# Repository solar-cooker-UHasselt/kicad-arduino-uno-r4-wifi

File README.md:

# solar-cooker-kicad-arduino-uno-r4-wifi

## TODO

- USB connector footprint giving DRC errors
- fix other remaining DRC errors
- complete BOM data
- check supplier if stock is still available
- check if alternative parts are a valid replacement

## Schematic importing errors

- Parameter Set not currently supported.
- Blanket not currently supported.

## Board improting errors

- Altium layer (71) has no KiCad equivalent. It has been moved to KiCad layer Eco1_User.
- Altium layer (72) has no KiCad equivalent. It has been moved to KiCad layer Eco1_User.
- Footprint J3 pad 1-6 uses a complex pad stack (not yet supported.)
- Footprint J6 pad 1-6 uses a complex pad stack (not yet supported.)

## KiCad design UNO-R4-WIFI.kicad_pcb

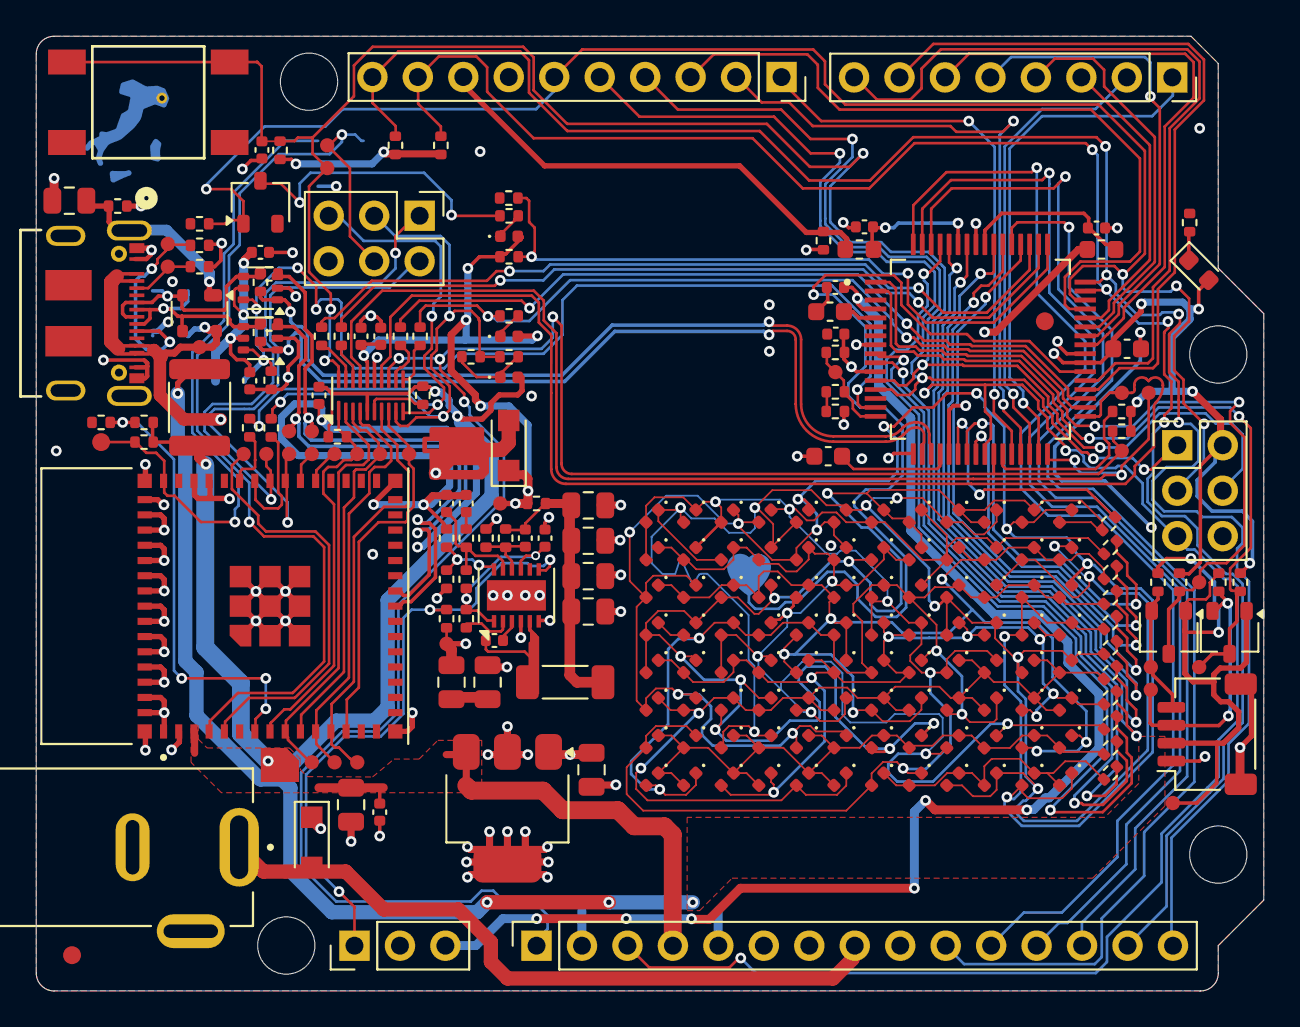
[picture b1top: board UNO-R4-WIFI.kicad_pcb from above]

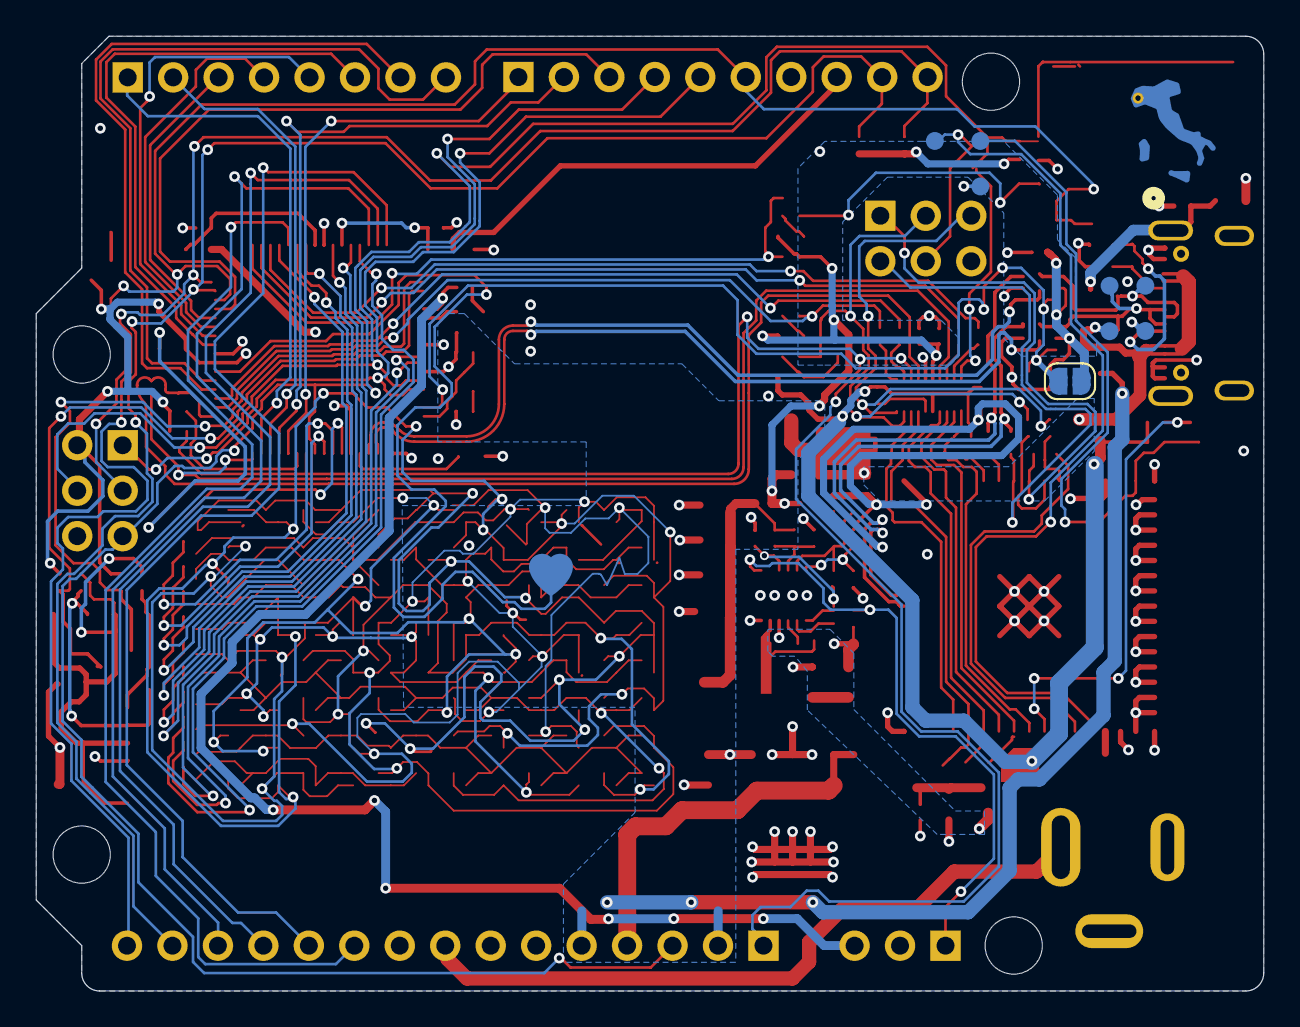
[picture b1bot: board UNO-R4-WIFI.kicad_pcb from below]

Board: 4 copper layers, 68.6 x 53.3 mm, 262 parts (9 on the bottom side), 121 nets.

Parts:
3V3_IC1, 3V3_TOP1, 5V_TOP1: TP-0.8MM
BUCK_IN_TOP1: TP-0.8MM
C1: DNP; C_0402_1005Metric
C2, C5, C9: 4.7uF; C_0603_1608Metric
C3, C7, C8, C11, C12, C25, C26, C29, C30: 100nF; C_0402_1005Metric
C6, C20, C24: 1uF; C_0402_1005Metric
C10, C13, C15, C16, C17, C18, C19, C28: 22uF; C_0805_2012Metric
C14: 33pF; C_0402_1005Metric
C21: 4.7nF; C_0805_2012Metric
C22: 1nF; C_0402_1005Metric
C23: 100pF; C_0402_1005Metric
CC1, CC2: TP-0.8MM
D1, D2, D3, D4, D5, D6, D7, D8, D9, D10, D11, D12, D13, D14, D15, D16, D17, D18, D19, D20, D21, D22, D23, D24, D25, D26, D27, D28, D29, D30, D31, D32, D33, D34, D35, D36, D37, D38, D39, D40, D41, D42, D43, D44, D45, D46, D47, D48, D49, D50, D51, D52, D53, D54, D55, D56, D57, D58, D59, D60, D61, D62, D63, D64, D65, D66, D67, D68, D69, D70, D71, D72, D73, D74, D75, D76, D77, D78, D79, D80, D81, D82, D83, D84, D85, D86, D87, D88, D89, D90, D91, D92, D93, D94, D95, D96: 150040RS73240; LED_0402_1005Metric
D97: PRTR5V0U2X,215; SOT-143
D98, D99: PMEG6020AELRX; Nexperia_CFP3_SOD-123W
D+1: TP-1.00MM
D+_TOP1: TP-0.8MM
D-1: TP-1.00MM
D-_TOP1: TP-0.8MM
DL1, DL2, DL4: APT1608YC; LED_0402_1005Metric
DL3: HSMG-C190; LED_0603_1608Metric
ESP_DOWNLOAD_BOTTOM1: TP-1.00MM
ESP_DOWNLOAD_TOP1: TP-0.8MM
ESP_EN_BOTTOM1: TP-1.00MM
ESP_EN_TOP1: TP-0.8MM; TP-1.00MM
ESP_IO1, ESP_IO4, ESP_IO5, ESP_IO6, ESP_IO7, ESP_IO8, ESP_IO9: TP-0.8MM
ESP_MTCK1: TP-0.8MM
ESP_MTDI1: TP-0.8MM
ESP_MTDO1: TP-0.8MM
ESP_MTMS1: TP-0.8MM
EXT_SCL1: TP-0.8MM
EXT_SDA1: TP-0.8MM
F1: MF-MSMF050-2; Fuse_1812_4532Metric
Fiducial_1, Fiducial_2: Fiducial mark 1mm with 2mm solder; Fiducial_1mm_Mask2mm
GND1, GND2: TP-1.00MM
H1, H2, H3, H4: MountingHole; MountingHole_3.2mm_M3_ISO7380
IC1, IC2: 74LVC1G3157DW-7; SOT-363_SC-70-6
IC3: ISL854102FRZ-T; DFN-12-1EP_3x4mm_P0.5mm_EP1.7x3.3mm
IC4: SGM2205-3.3XKC3G/TR; SOT-223
J1: GPHA-1X03; PinHeader_1x03_P2.54mm_Vertical
J2: SSQ-110-01-G-S; PinSocket_1x10_P2.54mm_Vertical
J3, J9: GPHA-2X03; PinHeader_2x03_P2.54mm_Vertical
J4: SSQ-108-01-G-S; PinSocket_1x08_P2.54mm_Vertical
J5: SSQ-115-01-G-S; PinSocket_1x15_P2.54mm_Vertical
J6: SM04B-SRSS-TB; JST_SH_SM04B-SRSS-TB_1x04-1MP_P1.00mm_Horizontal
J7: CX90B-16P
J8: EJ508A
L1, L2: BLM18PG471SN1D; L_0603_1608Metric
L3: PMF42-103MN; L_1806_4516Metric
LOVE1: TP-1.00MM
M1: ESP32-S3-MINI-1-N8
MD1: TP-0.8MM
P400_SCL1, P401_SDA1: TP-0.8MM
Q1, Q2, Q3: 2N7002KT1G; SOT-23W
R1, R3, R26, R35, R38, R43, R44, R49, R52, R56, R57, R58, R59: 100k; R_0402_1005Metric
R2, R14, R16, R20, R22, R23, R24, R25, R27, R28, R29, R30, R31, R32, R33, R34: 330; R_0402_1005Metric
R4, R5, R6, R7, R8, R9, R10, R11, R12, R13, R15, R19, R50, R51: 5.1k; R_0402_1005Metric
R17, R18, R21, R36, R37, R42, R45, R46, R47, R48, R53, R54, R55: 0; R_0402_1005Metric
R39: 1M; R_0402_1005Metric
R40, R60: 13k; R_0402_1005Metric
R41: 249k; R_0402_1005Metric
RES1: TP-0.8MM
SJ1: SMD solder JUMPER 0805; SolderJumper-2_P1.3mm_Open_RoundedPad1.0x1.5mm
SW1: FSM2JSMATR
SWCLK1: TP-0.8MM
SWDIO1: TP-0.8MM
U1: R7FA4M1AB3CFM#AA0
U2: TXB0108DQSR; USON-20_2x4mm_P0.4mm
VBUS_CONN1: TP-1.00MM
VCONN_TOP1: TP-0.8MM
VIN_TOP1: TP-0.8MM
uC_VBUS1: TP-0.8MM

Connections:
+3.3V: 3V3_TOP1.1, C10.1, C11.1, C26.1, DL2.2 (A), F1.1, IC4.3 (OUT_(3V3)), J5.4 (3V3), M1.3 (3V3), R26.1, R49.2, R56.1, R58.1, U2.5 (VCCA)
+3.3V_I2C: 3V3_IC1.1, F1.2, J6.2, Q1.1 (G), Q2.1 (G), R9.1, R11.1
+5V: 5V_TOP1.1, C2.2, C3.2, C24.1, C25.1, C28.1, C29.1, C30.1, D99.1 (K), DL1.2 (A), DL3.2 (A), DL4.2 (A), IC1.5 (VCC), IC2.5 (VCC), IC4.1 (IN), J3.2, J5.2 (IOREF), J5.5 (5V), L2.1, R3.1, R4.1, R5.1, R6.1, R7.1, R8.1, R10.1, R12.1, R13.1, R36.2, R59.1, SJ1.1, U1.11 (VCC), U1.21 (VCC_USB_LDO), U1.39 (VCC), U2.16 (VCCB)
/AREF: J2.8 (AREF), L1.1, R6.2
/CC1: CC1.1, J7.A5 (CC1), R50.1
/CC2: CC2.1, J7.B5 (CC2), R51.1
/ESP32_ENABLE: ESP_EN_BOTTOM1.1, ESP_EN_TOP1.1, M1.45 (EN), R26.2
/ESP_DOWNLOAD: ESP_DOWNLOAD_BOTTOM1.1, ESP_DOWNLOAD_TOP1.1, J9.4, M1.4 (BOOT_GPIO0)
/ESP_IO1: ESP_IO1.1, M1.5 (ADC1CH0_GPIO1)
/ESP_IO4: ESP_IO4.1, M1.8 (ADC1CH3_GPIO4), R58.2, U2.1 (A1)
/ESP_IO5: ESP_IO5.1, M1.9 (ADC1CH4_GPIO5), U2.2 (A2)
/ESP_IO6: ESP_IO6.1, M1.10 (ADC1CH5_GPIO6), U2.3 (A3)
/ESP_IO7: ESP_IO7.1, M1.11 (ADC1CH6_GPIO7), U2.4 (A4)
/ESP_IO8: ESP_IO8.1, M1.12 (ADC1CH7_GPIO8), U2.7 (A5)
/ESP_IO9: ESP_IO9.1, M1.13 (ADC1CH8_GPIO9), U2.8 (A6)
/ESP_IO41: ESP_MTDI1.1, J9.2, M1.37 (MTDI_GPIO41)
/ESP_IO42: ESP_MTMS1.1, J9.1, M1.38 (MTMS_GPIO42)
/ESP_MTCK: ESP_MTCK1.1, M1.35 (MTCK_GPIO39)
/ESP_MTDO: ESP_MTDO1.1, M1.36 (MTDO_GPIO40)
/ESP_N: D-_TOP1.1, IC2.3 (B0), M1.23 (USBDN_ADC2CH8_GPIO19), R53.2
/ESP_P: D+_TOP1.1, IC1.3 (B0), M1.24 (USBDP_ADC2CH9_GPIO20), R21.2
/ESP_RXD0: J9.5, R18.2, U2.10 (A8)
/ESP_TXD0: J9.3, R17.2, R20.2, R23.2, U2.9 (A7)
/EXT_SCL: EXT_SCL1.1, J6.4, Q1.2 (S), R9.2
/EXT_SDA: EXT_SDA1.1, J6.3, Q2.2 (S), R11.2
/ISL_VCC: C20.1, IC3.1 (SS), IC3.9 (VCC), R37.1, R42.2
/LED-MATRIX/ROW0: D1.2 (A), D2.1 (K), D3.2 (A), D4.1 (K), D7.2 (A), D8.1 (K), D13.2 (A), D14.1 (K), D21.2 (A), D22.1 (K), D31.2 (A), D32.1 (K), D43.2 (A), D44.1 (K), D57.2 (A), D58.1 (K), D73.2 (A), D74.1 (K), D91.2 (A), D92.1 (K), R2.2
/LED-MATRIX/ROW1: D1.1 (K), D2.2 (A), D5.2 (A), D6.1 (K), D9.2 (A), D10.1 (K), D15.2 (A), D16.1 (K), D23.2 (A), D24.1 (K), D33.2 (A), D34.1 (K), D45.2 (A), D46.1 (K), D59.2 (A), D60.1 (K), D75.2 (A), D76.1 (K), D93.2 (A), D94.1 (K), R14.2
/LED-MATRIX/ROW2: D3.1 (K), D4.2 (A), D5.1 (K), D6.2 (A), D11.2 (A), D12.1 (K), D17.2 (A), D18.1 (K), D25.2 (A), D26.1 (K), D35.2 (A), D36.1 (K), D47.2 (A), D48.1 (K), D61.2 (A), D62.1 (K), D77.2 (A), D78.1 (K), D95.2 (A), D96.1 (K), R16.2
/LED-MATRIX/ROW3: D7.1 (K), D8.2 (A), D9.1 (K), D10.2 (A), D11.1 (K), D12.2 (A), D19.2 (A), D20.1 (K), D27.2 (A), D28.1 (K), D37.2 (A), D38.1 (K), D49.2 (A), D50.1 (K), D63.2 (A), D64.1 (K), D79.2 (A), D80.1 (K), R27.2
/LED-MATRIX/ROW4: D13.1 (K), D14.2 (A), D15.1 (K), D16.2 (A), D17.1 (K), D18.2 (A), D19.1 (K), D20.2 (A), D29.2 (A), D30.1 (K), D39.2 (A), D40.1 (K), D51.2 (A), D52.1 (K), D65.2 (A), D66.1 (K), D81.2 (A), D82.1 (K), R28.2
/LED-MATRIX/ROW5: D21.1 (K), D22.2 (A), D23.1 (K), D24.2 (A), D25.1 (K), D26.2 (A), D27.1 (K), D28.2 (A), D29.1 (K), D30.2 (A), D41.2 (A), D42.1 (K), D53.2 (A), D54.1 (K), D67.2 (A), D68.1 (K), D83.2 (A), D84.1 (K), R29.2
/LED-MATRIX/ROW6: D31.1 (K), D32.2 (A), D33.1 (K), D34.2 (A), D35.1 (K), D36.2 (A), D37.1 (K), D38.2 (A), D39.1 (K), D40.2 (A), D41.1 (K), D42.2 (A), D55.2 (A), D56.1 (K), D69.2 (A), D70.1 (K), D85.2 (A), D86.1 (K), R30.2
/LED-MATRIX/ROW7: D43.1 (K), D44.2 (A), D45.1 (K), D46.2 (A), D47.1 (K), D48.2 (A), D49.1 (K), D50.2 (A), D51.1 (K), D52.2 (A), D53.1 (K), D54.2 (A), D55.1 (K), D56.2 (A), D71.2 (A), D72.1 (K), D87.2 (A), D88.1 (K), R31.2
/LED-MATRIX/ROW8: D57.1 (K), D58.2 (A), D59.1 (K), D60.2 (A), D61.1 (K), D62.2 (A), D63.1 (K), D64.2 (A), D65.1 (K), D66.2 (A), D67.1 (K), D68.2 (A), D69.1 (K), D70.2 (A), D71.1 (K), D72.2 (A), D89.2 (A), D90.1 (K), R32.2
/LED-MATRIX/ROW9: D73.1 (K), D74.2 (A), D75.1 (K), D76.2 (A), D77.1 (K), D78.2 (A), D79.1 (K), D80.2 (A), D81.1 (K), D82.2 (A), D83.1 (K), D84.2 (A), D85.1 (K), D86.2 (A), D87.1 (K), D88.2 (A), D89.1 (K), D90.2 (A), R33.2
/LED-MATRIX/ROW10: D91.1 (K), D92.2 (A), D93.1 (K), D94.2 (A), D95.1 (K), D96.2 (A), R34.2
/MD: J5.1 (NC), MD1.1, R8.2, U1.26 (MD/P201), U2.13 (B6)
/OFF: IC3.7 (EN), J1.1, R35.2
/P000_AN00_AMP+: J5.11 (A1), U1.64 (AN000/P000)
/P001_AN01_AMP-: J5.12 (A2), U1.63 (AN001/P001)
/P002_AN02_AMPO: J5.13 (A3), U1.62 (AN002/P002)
/P003: R28.1, U1.61 (AN003/P003)
/P004: R31.1, U1.60 (AN004/P004)
/P011: R32.1, U1.58 (VREFL0/AN006/P011)
/P012: R14.1, U1.55 (VREFH/AN007/P012)
/P013: R16.1, U1.54 (VREFL/AN008/P013)
/P014_AN09_DAC: J5.10 (A0), U1.53 (DA0/AN009/P014)
/P015: R30.1, U1.52 (AN010/P015)
/P100_AN22_SCL: J2.10 (SCL), J5.15 (A5), R4.2, U1.48 (GTIOC5B/AN022/P100)
/P101_AN21_SDA: J2.9 (SDA), J5.14 (A4), R5.2, U1.47 (GTIOC5A/AN021/P101)
/P102_SPI0_RSPCK_GPT2_B_CAN0_RX: J2.6 (D13/SCK), J3.3, Q3.1 (G), R52.1, U1.46 (ADTRG0/GTIOC2B/AN020/P102)
/P103_SPI0_SSL_GPT2_A_CAN0_TX: J2.3 (D10/CS), U1.45 (GTIOC2A/AN019/P103)
/P104_IRQ01_GPT1_B: J4.3 (D2), U1.44 (GTIOC1B/P104)
/P105_IRQ00_GPT1_A: J4.4 (D3), U1.43 (GTIOC1A/P105)
/P106_GPT0_B: J4.5 (D4), U1.42 (GTIOC0B/P106)
/P107_GPT0_A: J4.6 (D5), U1.41 (GTIOC0A/P107)
/P108_SWDIO: SWDIO1.1, U1.33 (P108/GTIOC0B/TMS/SWDIO), U2.14 (B5)
/P109_SCI9_TXD: R22.2, R48.1, U1.34 (CTX0/TDO/SWO/GTIOC1A/P109)
/P110_SCI9_RXD: R47.1, U1.35 (CRX0/TDI/GTIOC1B/P110)
/P111_GPT3_A: J4.7 (D6), U1.36 (GTIOC3A/P111)
/P112_GPT3_B: J4.8 (D7), U1.37 (GTIOC3B/P112)
/P204: R29.1, U1.24 (GTIOC4B/P204)
/P205: R2.1, U1.23 (GTIOC4A/P205)
/P206: R27.1, U1.22 (P206)
/P212: R34.1, U1.10 (P212/GTIOC0B/EXTAL)
/P213: R33.1, U1.9 (P213/GTIOC0A/XTAL)
/P300_SWCLK: SWCLK1.1, U1.32 (P300/GTIOC0A/TCK/SWCLK), U2.17 (B4)
/P301_SCI2_RXD: J4.1 (D0/RX), U1.31 (GTIOC4B/P301)
/P302_SCI2_TXD: J4.2 (D1/TX), U1.30 (GTIOC4A/P302)
/P303_GPT7_B: J2.2 (D9), U1.29 (GTIOC7B/P303)
/P304_GPT7_A: J2.1 (D8), U1.28 (GTIOC7A/P304)
/P400_IIC0_SCL: P400_SCL1.1, Q1.3 (D), R10.2, U1.1 (P400/GTIOC6A)
/P401_IIC0_SDA: P401_SDA1.1, Q2.3 (D), R12.2, U1.2 (P401/GTIOC6B/CTX0)
/P408: IC1.6 (SELECT), IC2.6 (SELECT), R1.1, SJ1.2, U1.15 (P408/GTIOC5B/USB_ID)
/P410_SPI0_MISO_GPT6_B: J2.5 (D12/MISO), J3.1, U1.13 (P410/GTIOC6B)
/P411_SPI0_MOSI_GPT6_A: J2.4 (D11/MOSI), J3.4, U1.12 (P411/GTIOC6A)
/P501_SCI1_TXD: R45.1, U1.50 (GTIOC2B/AN017/P501)
/P502_SCI1_RXD: R46.1, U1.51 (GTIOC3B/AN018/P502)
/RA4_N: IC2.1 (B1), R55.2, U1.18 (P915/USB_DM)
/RA4_P: IC1.1 (B1), R54.2, U1.19 (P914/USB_DP)
/SHIELD1: C21.1, D97.1 (GND), J7.S1 (SHIELD), R39.1
/USB_D_N: D97.3 (I/O2), D-1.1, IC2.4 (A), J7.A7 (D-), J7.B7 (D-), R53.1, R55.1
/USB_D_P: D97.2 (I/O1), D+1.1, IC1.4 (A), J7.A6 (D+), J7.B6 (D+), R21.1, R54.1
/VBATT: C8.1, J1.3, U1.4 (VBATT)
/VREFH0: C7.1, L1.2, U1.59 (P010/AN005/VREFH0)
/~RESET: C1.1, J3.5, J5.3 (RESET), R3.2, RES1.1, SW1.3, SW1.4, U1.25 (~RES), U2.20 (B1)
GND: C1.2, C2.1, C3.1, C5.1, C6.2, C7.2, C8.2, C9.2, C10.2, C11.2, C15.2, C16.2, C17.2, C18.2, C19.2, C20.2, C21.2, C22.2, C23.2, C24.2, C25.2, C26.2, C28.2, C29.2, C30.2, GND1.1, GND2.1, IC1.2 (GND), IC2.2 (GND), IC3.6 (PGND), IC3.13 (GNDPAD), IC4.2 (GND), IC4.4 (GND), J1.2, J2.7 (GND), J3.6, J5.6 (GND), J5.7 (GND), J6.1, J6.5, J7.A1 (GND), J7.A12 (GND), J7.B1 (GND), J7.B12 (GND), J8.2, J8.3, J9.6, M1.1 (GND), M1.2 (GND), M1.42 (GND), M1.43 (GND), M1.46 (GND), M1.47 (GND), M1.48 (GND), M1.49 (GND), M1.50 (GND), M1.51 (GND), M1.52 (GND), M1.53 (GND), M1.54 (GND), M1.55 (GND), M1.56 (GND), M1.57 (GND), M1.58 (GND), M1.59 (GND), M1.60 (GND), M1.61 (GND), M1.62 (GND), M1.63 (GND), M1.64 (GND), M1.65 (GND), Q3.2 (S), R1.2, R19.2, R24.2, R39.2, R40.2, R43.2, R44.2, R50.2, R51.2, R52.2, R57.2, R60.2, SW1.1, SW1.2, U1.8 (VSS), U1.17 (VSS_USB), U1.40 (VSS), U1.57 (AVSS0), U2.15 (GND)
unnamed: C13.2, C19.1
unnamed: C14.1, C15.1, C16.1, C17.1, C18.1, L3.2, R36.1, R38.1
unnamed: C22.1, R41.2
unnamed: BUCK_IN_TOP1.1, C13.1, D98.1 (K), IC3.4 (VIN), R35.1
unnamed: DL1.1 (K), R22.1
unnamed: DL2.1 (K), R20.1, R23.1
unnamed: DL3.1 (K), R24.1
unnamed: DL4.1 (K), R25.1
unnamed: C12.1, IC3.3 (BOOT)
unnamed: C23.1, IC3.11 (COMP), R41.1, R42.1
unnamed: C14.2, IC3.10 (FB), R38.2, R40.1
unnamed: IC3.12 (FS), R43.1, R44.1
unnamed: C12.2, IC3.5 (PHASE), L3.1
unnamed: IC3.2 (SYNC), R37.2
unnamed: M1.7 (ADC1CH2_GPIO3), R56.2, R57.1
unnamed: M1.40 (U0RXD/GPIO44), R18.1
unnamed: M1.39 (U0TXD/GPIO43), R17.1
unnamed: Q3.3 (D), R25.2
unnamed: R15.2, R19.1
unnamed: C6.1, L2.2, U1.56 (AVCC0)
unnamed: R59.2, R60.1, U1.49 (GTIOC2A/AN016/P500)
unnamed: LOVE1.1, U1.38 (GTIOC2A/P113)
unnamed: R7.2, U1.27 (NMI/INPUT_ONLY_P200)
unnamed: R13.2, R15.1, U1.16 (P407/USB_VBUS/ADTRG0), uC_VBUS1.1
unnamed: C5.2, U1.20 (VCC_USB)
unnamed: C9.1, U1.5 (VCL)
unnamed: R46.2, U2.19 (B2)
unnamed: R45.2, U2.18 (B3)
unnamed: R47.2, U2.12 (B7)
unnamed: R48.2, U2.11 (B8)
unnamed: R49.1, U2.6 (OE)
VIN: D98.2 (A), J5.8 (VIN), J8.1, VIN_TOP1.1
VUSB: D97.4 (VCC), D99.2 (A), J7.A4 (VBUS), J7.A9 (VBUS), J7.B4 (VBUS), J7.B9 (VBUS), VBUS_CONN1.1, VCONN_TOP1.1

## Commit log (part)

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2024-03-04 blank KiCad project
2024-03-04 Altium import
2024-03-04 added Altium STEP models
2024-03-04 annotation update
2024-03-04 added 3D models
2024-03-04 updated test points + schematic readability improvement
2024-03-05 updated test points footprints
2024-03-05 updated resistor schematic + footprints
2024-03-05 fixed missing footprints
2024-03-06 added drawing sheet
2024-03-07 added external schematic library
2024-03-11 changed power symbols
2024-03-11 updated capacitors symbols + footprints
2024-03-11 usb connector symbol + footprint update
2024-03-12 fixed LED matrix routing
2024-03-13 silkscreen update
2024-04-01 changed ESD protection symbol in schematic
2024-04-01 changed last symbols in schematic
2024-04-01 fixed multiple DRC errors
2024-04-01 update arduino schematic
2024-04-03 changed copper finish + solder mask and silkscreen color update + drc exclusion fix
2024-04-03 silkscreen update + ESP32 footprint update
2024-04-04 KiBot DRC check workflow
2024-04-05 layer update
2024-04-05 no more update PCB from schematic errors
2024-04-05 fixed schematic parity + silkscreen update
2024-04-06 fixed DRC errors + microcontroller footprint pad size update
2024-04-08 several DRC fixes + dnp components update
2024-04-09 removed unused footprints + footprints name change + 3D models update
2024-04-09 removed unused symbols + removed Altium import leftovers
2024-04-09 BOM update (incomplete)
2024-04-10 switched to generic pin headers from Eurocircuits + other BOM improvements
2024-04-10 added DRC exclusions
2024-04-12 board outline fix
2024-04-16 exclude from BOM update + USB connector footprint update + Eurocircuits DRC fixes
